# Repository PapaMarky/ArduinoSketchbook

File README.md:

ArduinoLibs
===========

Libraries for Arduino programming

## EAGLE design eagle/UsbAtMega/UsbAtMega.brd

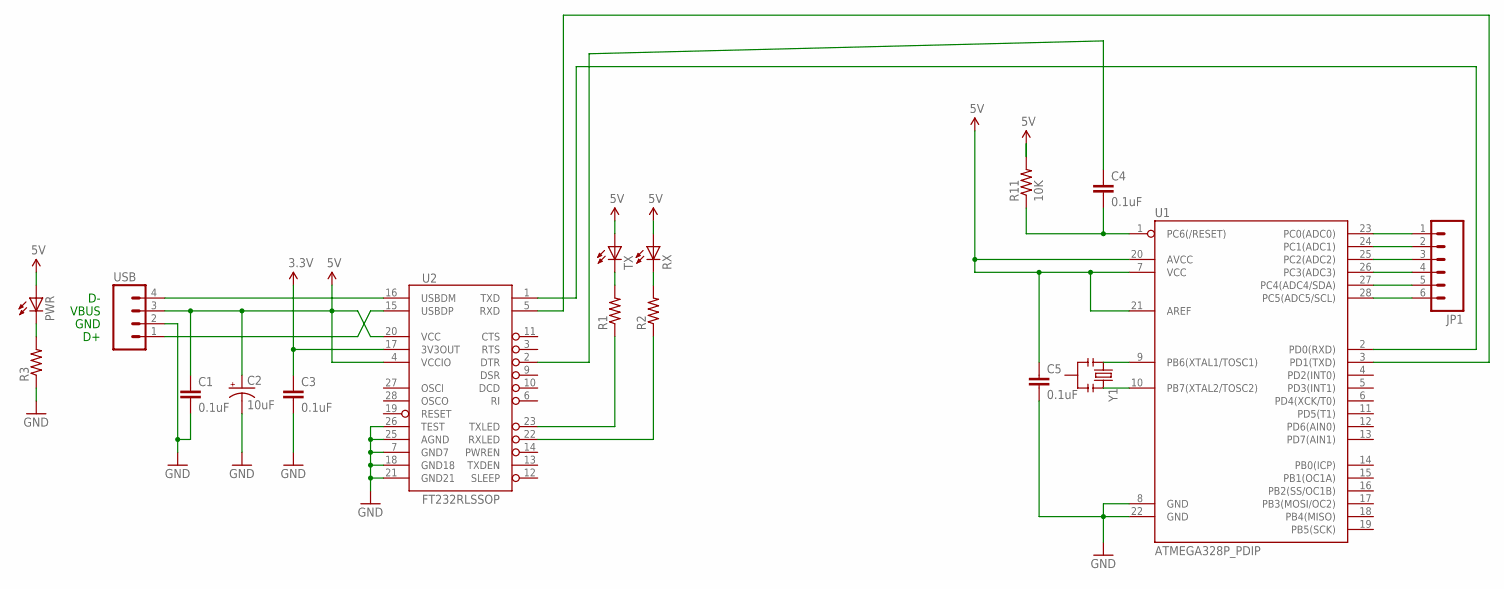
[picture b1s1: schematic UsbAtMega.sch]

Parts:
C1, C3: 0.1uF; CAP-PTH-SMALLEZ
C2: 10uF; CPOL-RADIAL-10UF-25V
C4, C5: 0.1uF; CAP-PTH-SMALL
JP1: M06SIP; 1X06
PWR: LED5MM
R1, R2, R3: 10KOHM1/6W5%(PTH)KIT; AXIAL-0.3-KIT
R11: 10K; AXIAL-0.3
RX: LED5MM
TX: LED5MM
U1: ATMEGA328P_PDIP; DIL28-3
U2: FT232RLSSOP; SSOP28DB
USB: M04LOCK; 1X04_LOCK
Y1: RESONATORPTH; RESONATOR-PTH

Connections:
3.3V: C3.1, U2.17 (3V3OUT)
5V: C1.1, C2.1 (+), C5.1, PWR.A, R11.P$2 (2), RX.A, TX.A, U1.7 (VCC), U1.20 (AVCC), U1.21 (AREF), U2.4 (VCCIO), U2.20 (VCC), USB.3
GND: C1.2, C2.2 (-), C3.2, C5.2, R3.P$1 (1), U1.8 (GND), U1.22 (GND), U2.7 (GND7), U2.18 (GND18), U2.21 (GND21), U2.25 (AGND), U2.26 (TEST), USB.2
unnamed: C4.2, R11.P$1 (1), U1.1 (PC6(/RESET))
unnamed: U2.16 (USBDM), USB.4
unnamed: U2.15 (USBDP), USB.1
unnamed: C4.1, U2.2 (DTR)
unnamed: U1.2 (PD0(RXD)), U2.1 (TXD)
unnamed: U1.3 (PD1(TXD)), U2.5 (RXD)
unnamed: U1.9 (PB6(XTAL1/TOSC1)), Y1.1
unnamed: U1.10 (PB7(XTAL2/TOSC2)), Y1.3
unnamed: JP1.6, U1.28 (PC5(ADC5/SCL))
unnamed: JP1.5, U1.27 (PC4(ADC4/SDA))
unnamed: JP1.4, U1.26 (PC3(ADC3))
unnamed: JP1.3, U1.25 (PC2(ADC2))
unnamed: R1.P$1 (1), U2.23 (TXLED)
unnamed: R2.P$1 (1), U2.22 (RXLED)
unnamed: R1.P$2 (2), TX.K (C)
unnamed: R2.P$2 (2), RX.K (C)
unnamed: PWR.K (C), R3.P$2 (2)
unnamed: JP1.2, U1.24 (PC1(ADC1))
unnamed: JP1.1, U1.23 (PC0(ADC0))

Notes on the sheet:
VBUS
GND

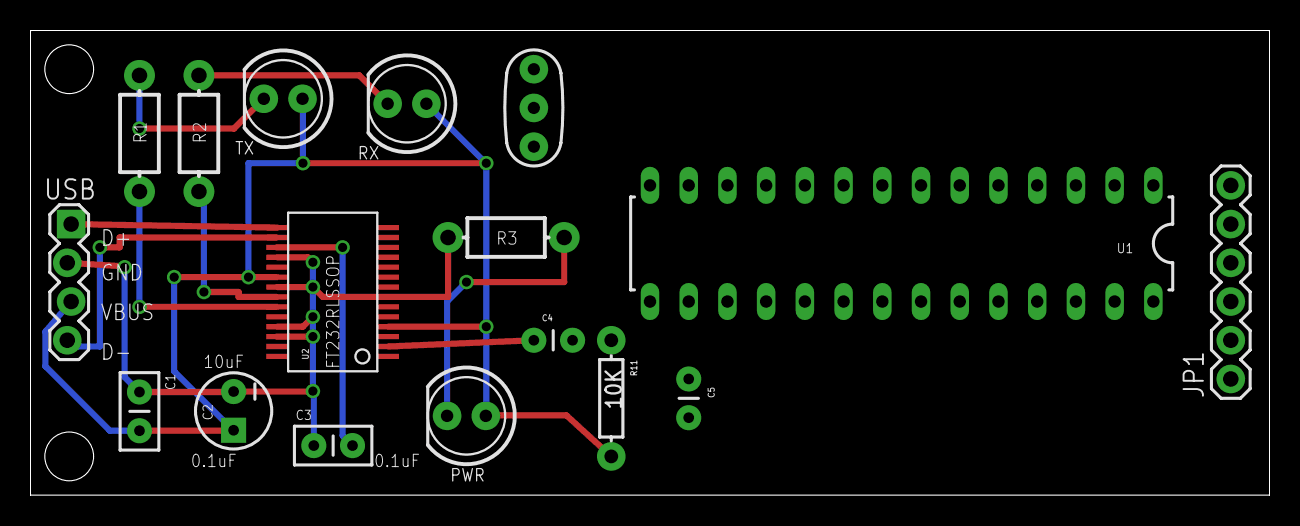
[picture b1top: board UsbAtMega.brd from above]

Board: 2 copper layers, 81.3 x 30.5 mm, 17 parts (0 on the bottom side), 22 nets.

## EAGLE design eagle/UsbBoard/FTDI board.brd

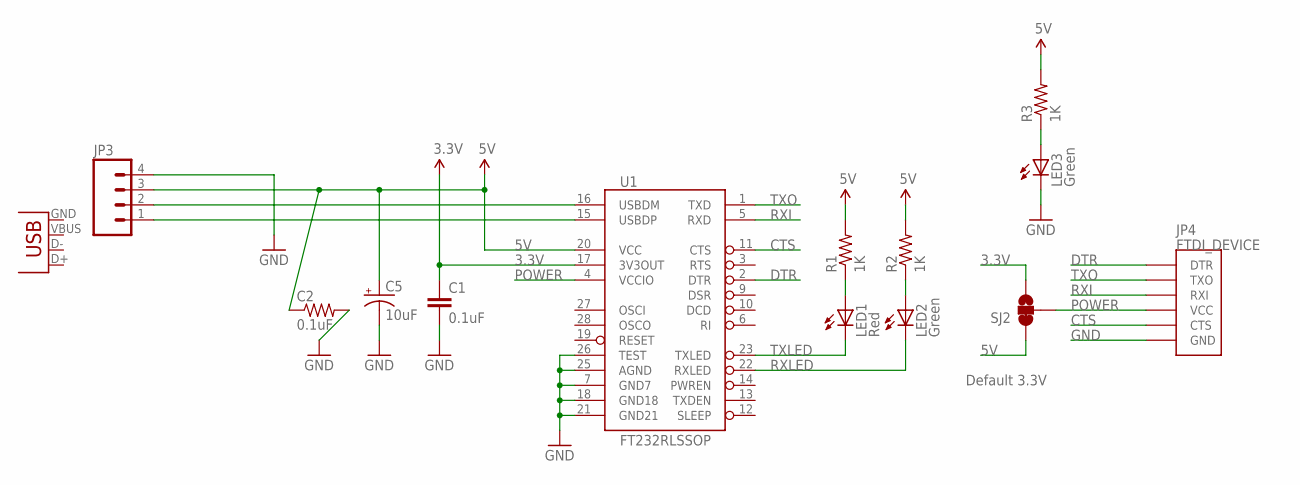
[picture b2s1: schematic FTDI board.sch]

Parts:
C1: 0.1uF; 0402-CAP
C2: 0.1uF; AXIAL-0.1
C5: 10uF; EIA3216
JP3: M04LOCK; 1X04_LOCK
JP4: FTDI_DEVICE; FTDI_DEVICE_SIDE
LED1: Red; LED5MM
LED2, LED3: Green; LED5MM
R1, R2, R3: 1K; AXIAL-0.1
SJ2: SOLDERJUMPER_2WAYS; SJ_3
U1: FT232RLSSOP; SSOP28DB
X1: USB-SMD-NS; USB-MINIB-NOSTOP

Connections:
3.3V: C1.1, SJ2.3, U1.17 (3V3OUT)
5V: C2.P$1 (1), C5.A (+), JP3.3, R1.P$2 (2), R2.P$2 (2), R3.P$2 (2), SJ2.1, U1.20 (VCC)
CTS: JP4.P$5 (CTS), U1.11 (CTS)
DTR: JP4.P$1 (DTR), U1.2 (DTR)
GND: C1.2, C2.P$2 (2), C5.C (-), JP3.4, JP4.P$6 (GND), LED3.K (C), U1.7 (GND7), U1.18 (GND18), U1.21 (GND21), U1.25 (AGND), U1.26 (TEST)
unnamed: LED1.A, R1.P$1 (1)
unnamed: LED2.A, R2.P$1 (1)
unnamed: LED3.A, R3.P$1 (1)
POWER: JP4.P$4 (VCC), SJ2.2, U1.4 (VCCIO)
RXI: JP4.P$3 (RXI), U1.5 (RXD)
RXLED: LED2.K (C), U1.22 (RXLED)
TXLED: LED1.K (C), U1.23 (TXLED)
TXO: JP4.P$2 (TXO), U1.1 (TXD)
USB_D+: JP3.1, U1.15 (USBDP)
USB_D-: JP3.2, U1.16 (USBDM)

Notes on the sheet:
Default 3.3V

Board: 2 copper layers, 14 parts (1 on the bottom side), 15 nets, no tracks yet.

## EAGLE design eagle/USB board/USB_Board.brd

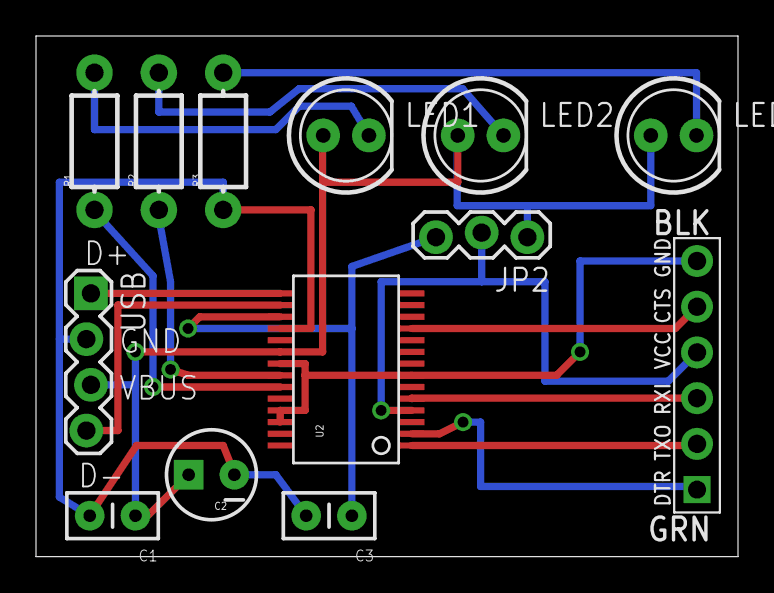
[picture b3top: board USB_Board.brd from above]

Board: 2 copper layers, 39.0 x 28.9 mm, 13 parts (0 on the bottom side), 15 nets.

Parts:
C1, C3: 0.1uF; CAP-PTH-SMALLEZ
C2: 10uF; CPOL-RADIAL-10UF-25V
JP1: FTDI_DEVICE; FTDI_DEVICE_SIDE
JP2: 1X03_LOCK
LED1, LED2, LED3: LED5MM
R1, R2, R3: AXIAL-0.3-KIT
U2: FT232RLSSOP; SSOP28DB
USB: 1X04_LOCK

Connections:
3.3V: C3.1, JP2.3, U2.17
5V: C1.1, C2.1, JP2.1, LED1.A, LED2.A, LED3.A, U2.20, USB.3
GND: C1.2, C2.2, C3.2, JP1.P$6, R3.P$1, U2.7, U2.18, U2.21, U2.25, U2.26, USB.2
unnamed: U2.16, USB.4
unnamed: U2.15, USB.1
unnamed: JP1.P$2, U2.1
unnamed: JP1.P$3, U2.5
unnamed: JP1.P$5, U2.11
unnamed: JP1.P$1, U2.2
unnamed: JP1.P$4, JP2.2, U2.4
unnamed: R1.P$1, U2.23
unnamed: R2.P$1, U2.22
unnamed: LED1.K, R1.P$2
unnamed: LED2.K, R2.P$2
unnamed: LED3.K, R3.P$2

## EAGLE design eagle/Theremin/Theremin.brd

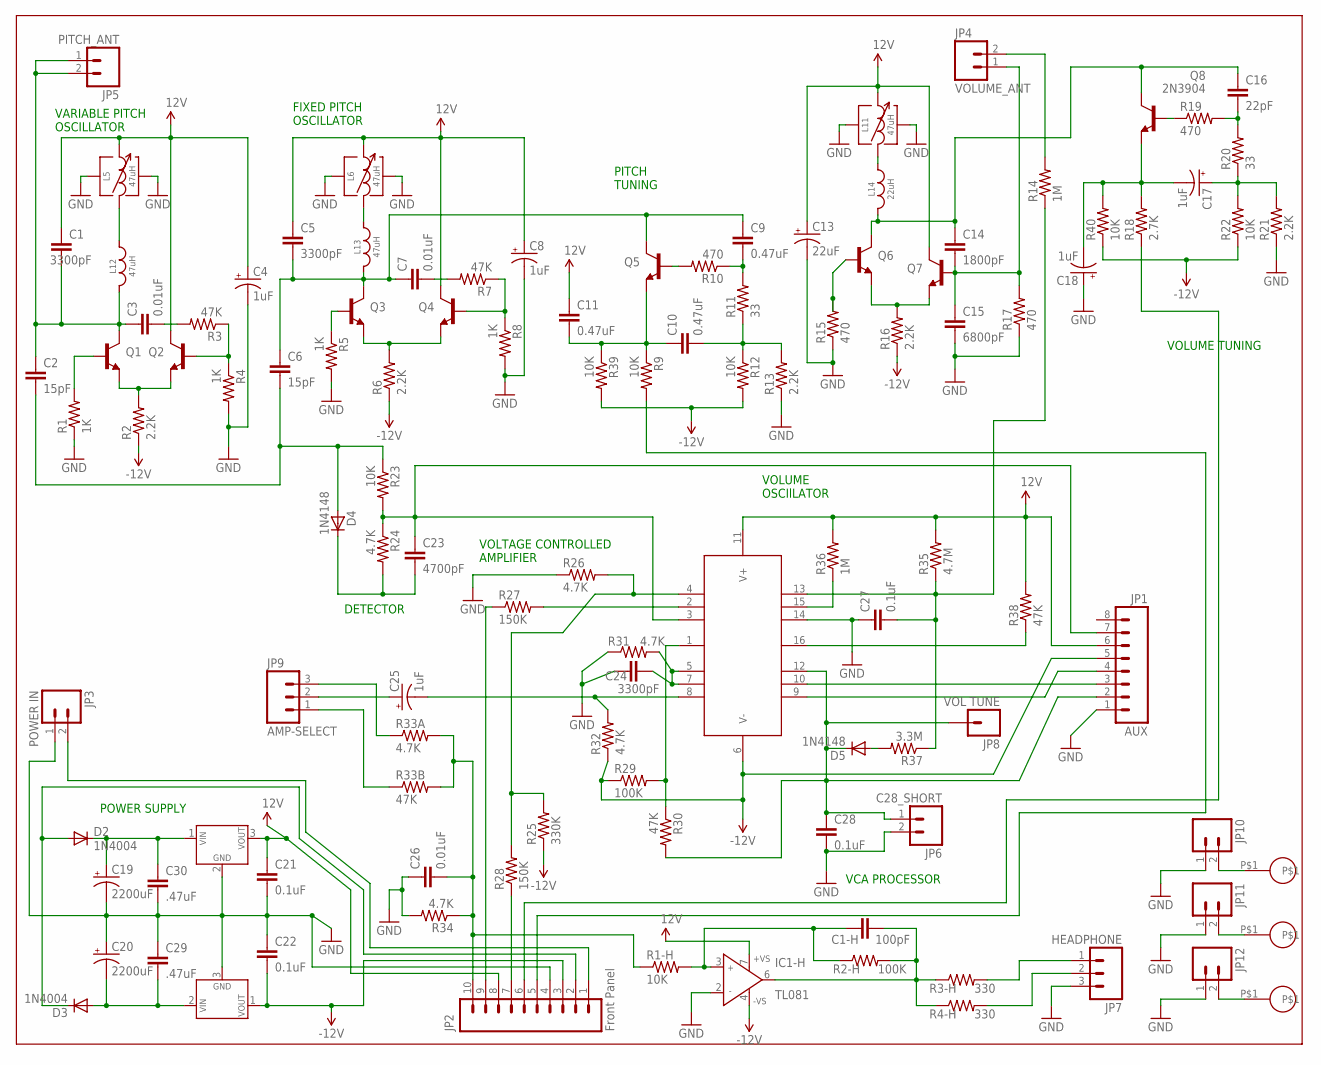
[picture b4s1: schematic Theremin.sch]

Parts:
C1, C5: 3300pF; 9M-CAP-RADIAL
C1-H: 100pF; CAP-PTH-SMALL
C2, C6: 15pF; CAP-PTH-SMALL
C3, C7, C26: 0.01uF; 5M-CAP-RADIAL
C4, C8, C17, C18, C25: 1uF; CPOL-RADIAL-10UF-25V
C9, C10, C11: 0.47uF; CAP-PTH-5MM
C13: 22uF; CPOL-RADIAL-1000UF-25V
C14: 1800pF; CAP-PTH-LARGE
C15: 6800pF; C5B3
C16: 22pF; CAP-PTH-SMALLEZ
C19, C20: 2200uF; 10MM-RADIAL-CPOL
C21, C22, C27, C28: 0.1uF; CAP-PTH-SMALL
C23: 4700pF; CAP-PTH-SMALL
C24: 3300pF; CAP-PTH-SMALL
C29, C30: .47uF; AXIAL-5MM
D2, D3: 1N4004; DO41-10
D4, D5: 1N4148; DIODE-1N4148
IC1-H: TL081; DIL08
JP1: AUX; 1X08
JP2: Front Panel; 1X10
JP3: POWER IN; 1X02_NO_SILK
JP4: VOLUME_ANT; 1X02_NO_SILK
JP5: PITCH_ANT; 1X02_NO_SILK
JP6: C28_SHORT; 1X02_LOCK
JP7: HEADPHONE; 1X03_NO_SILK
JP8: VOL TUNE; 1X01_LONGPAD
JP9: AMP-SELECT; 1X03_LOCK
JP10, JP11, JP12: M02LOCK; 1X02_LOCK
L5, L6, L11: 47uH; SLOT-TEN
L12, L13: 47uH; FIXED-INDUCTOR-API-DELEVAN
L14: 22uH; FIXED-INDUCTOR-API-DELEVAN
Q1, Q2, Q3, Q4, Q5, Q6, Q7, Q8: 2N3904; TO92
R1, R4, R5, R8: 1K; AXIAL-0.4
R1-H, R9, R12, R22, R23, R39, R40: 10K; AXIAL-0.4
R2, R6, R13, R16, R21: 2.2K; AXIAL-0.4
R2-H, R29: 100K; AXIAL-0.4
R3, R7, R30, R33B, R38: 47K; AXIAL-0.4
R3-H, R4-H: 330; AXIAL-0.4
R10, R15, R17, R19: 470; AXIAL-0.4
R11, R20: 33; AXIAL-0.4
R14, R36: 1M; AXIAL-0.4
R18: 2.7K; AXIAL-0.4
R24, R26, R31, R32, R33A, R34: 4.7K; AXIAL-0.4
R25: 330K; AXIAL-0.4
R27, R28: 150K; AXIAL-0.4
R35: 4.7M; AXIAL-0.4
R37: 3.3M; AXIAL-0.4
U1: LM78L12; TO-92
U2: LM79L12; TO-92
U3: LM13700N; DIL16
U$1, U$2, U$3: GROUND-SCREW

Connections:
5V: C1.P$1 (1), C4.1 (+), C5.P$1 (1), C8.1 (+), C11.1, C13.1 (+), C21.1, IC1-H.7 (+VS), JP1.6, JP2.8, L5.IN$1, L6.IN$1, L11.IN$1, Q2.1 (C), Q4.1 (C), Q7.1 (C), R35.P$2 (2), R36.P$2 (2), R38.P$2 (2), U1.3 (VOUT), U3.11 (V+)
-12V: JP1.5, R2.P$1 (1), R16.P$1 (1), R22.P$1 (1), R29.P$1 (1), R32.P$1 (1), R40.P$1 (1), U3.6 (V-)
GND: C4.2 (-), C8.2 (-), C13.2 (-), C15.2, C18.1 (+), C19.P$2 (-), C20.P$1 (+), C21.2, C22.1, C24.1, C26.P$1 (1), C27.1, C28.2, C29.P$1 (1), C30.P$2 (2), IC1-H.2 (IN-), JP1.1, JP2.4, JP3.1, JP6.2, JP7.3, JP10.1, JP11.1, JP12.1, L5.TAB@7, L5.TAB@8, L6.TAB@7, L6.TAB@8, L11.TAB@7, L11.TAB@8, R1.P$1 (1), R4.P$2 (2), R5.P$2 (2), R8.P$2 (2), R13.P$1 (1), R15.P$1 (1), R17.P$1 (1), R21.P$1 (1), R26.P$1 (1), R31.P$1 (1), R34.P$2 (2), U1.2 (GND), U2.3 (GND), U3.14 (IN-PLUS-B)
unnamed: Q8.2 (B), R19.P$1 (1)
unnamed: C16.2, R19.P$2 (2), R20.P$2 (2)
unnamed: C17.1 (+), R20.P$1 (1), R21.P$2 (2), R22.P$2 (2)
unnamed: C14.1, C16.1, L14.P$2, Q6.1 (C), Q8.1 (C)
unnamed: C17.2 (-), C18.2 (-), Q8.3 (E), R18.P$2 (2), R40.P$2 (2)
unnamed: Q6.3 (E), Q7.3 (E), R16.P$2 (2)
unnamed: JP2.6, R18.P$1 (1)
unnamed: Q6.2 (B), R15.P$2 (2)
unnamed: C14.2, C15.1, JP4.1, Q7.2 (B), R17.P$2 (2)
unnamed: L5.OUT$3 (OUT$2), L12.P$1
unnamed: L11.OUT$3 (OUT$2), L14.P$1
unnamed: C20.P$2 (-), C29.P$2 (2), D3.A, U2.2 (VIN)
unnamed: C19.P$1 (+), C30.P$1 (1), D2.C, U1.1 (VIN)
unnamed: D2.A, D3.C, JP2.2
unnamed: JP4.2, R14.P$2 (2)
unnamed: Q1.2 (B), R1.P$2 (2)
unnamed: C1.P$2 (2), C2.1, C3.P$1 (1), JP5.1, JP5.2, L12.P$2, Q1.1 (C)
unnamed: Q1.3 (E), Q2.3 (E), R2.P$2 (2)
unnamed: Q2.2 (B), R3.P$1 (1), R4.P$1 (1)
unnamed: C2.2, C6.2, D4.A, R23.P$1 (1)
unnamed: R38.P$1 (1), U3.16 (BIAS-IN-B)
unnamed: JP1.3, U3.10 (B-IN-B)
unnamed: JP1.4, U3.9 (B-OUT-B)
unnamed: C28.1, D5.C, JP1.2, JP6.1, JP8.1, R30.P$2 (2), U3.12 (OUT-B)
unnamed: D5.A, R37.P$2 (2)
unnamed: C27.2, R14.P$1 (1), R35.P$1 (1), R37.P$1 (1), U3.13 (IN-MINUS-B)
unnamed: R29.P$2 (2), R30.P$1 (1), U3.1 (BIAS-IN-A)
unnamed: R36.P$1 (1), U3.15 (DIODE-BIAS-B)
unnamed: C25.2 (-), R32.P$2 (2), U3.8 (B-OUT-A)
unnamed: C25.1 (+), JP9.2
unnamed: C1-H.1, IC1-H.3 (IN+), R1-H.P$2 (2), R2-H.P$1 (1)
unnamed: C24.2, R31.P$2 (2), U3.5 (OUT-A), U3.7 (B-IN-A)
unnamed: R27.P$2 (2), U3.2 (DIODE-BIAS-A)
unnamed: JP2.9, R27.P$1 (1)
unnamed: JP2.7, R28.P$1 (1)
unnamed: R25.P$2 (2), R26.P$2 (2), R28.P$2 (2), U3.4 (IN-MINUS-A)
unnamed: C23.1, JP1.7, R23.P$2 (2), R24.P$1 (1), U3.3 (IN-PLUS-A)
unnamed: C23.2, D4.C, R24.P$2 (2)
unnamed: JP2.1, JP3.2
unnamed: C3.P$2 (2), R3.P$2 (2)
unnamed: C5.P$2 (2), C6.1, C7.P$1 (1), C9.1, L13.P$2, Q3.1 (C), Q5.1 (C)
unnamed: Q3.2 (B), R5.P$1 (1)
unnamed: Q3.3 (E), Q4.3 (E), R6.P$2 (2)
unnamed: L6.OUT$3 (OUT$2), L13.P$1
unnamed: C10.1, C11.2, Q5.3 (E), R9.P$1 (1), R39.P$1 (1)
unnamed: C7.P$2 (2), R7.P$2 (2)
unnamed: JP2.5, R9.P$2 (2)
unnamed: Q4.2 (B), R7.P$1 (1), R8.P$1 (1)
unnamed: Q5.2 (B), R10.P$2 (2)
unnamed: C9.2, R10.P$1 (1), R11.P$2 (2)
unnamed: C10.2, R11.P$1 (1), R12.P$1 (1), R13.P$2 (2)
unnamed: JP9.3, R33A.P$1 (1)
unnamed: JP9.1, R33B.P$1 (1)
unnamed: C26.P$2 (2), JP2.10, R1-H.P$1 (1), R33A.P$2 (2), R33B.P$2 (2), R34.P$1 (1)
unnamed: C1-H.2, IC1-H.6 (OUT), R2-H.P$2 (2), R3-H.P$1 (1), R4-H.P$1 (1)
unnamed: JP7.1, R3-H.P$2 (2)
unnamed: JP7.2, R4-H.P$2 (2)
unnamed: JP10.2, U$2.P$1
unnamed: JP11.2, U$1.P$1
unnamed: JP12.2, U$3.P$1
VNEG: C22.2, IC1-H.4 (-VS), JP2.3, R6.P$1 (1), R12.P$2 (2), R25.P$1 (1), R39.P$2 (2), U2.1 (VOUT)

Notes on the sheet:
VOLUME TUNING
VOLUME OSCIlLATOR
POWER SUPPLY
VARIABLE PITCH OSCILLATOR
VCA PROCESSOR
VOLTAGE CONTROLLED AMPLIFIER
DETECTOR
FIXED PITCH OSCILLATOR
PITCH TUNING

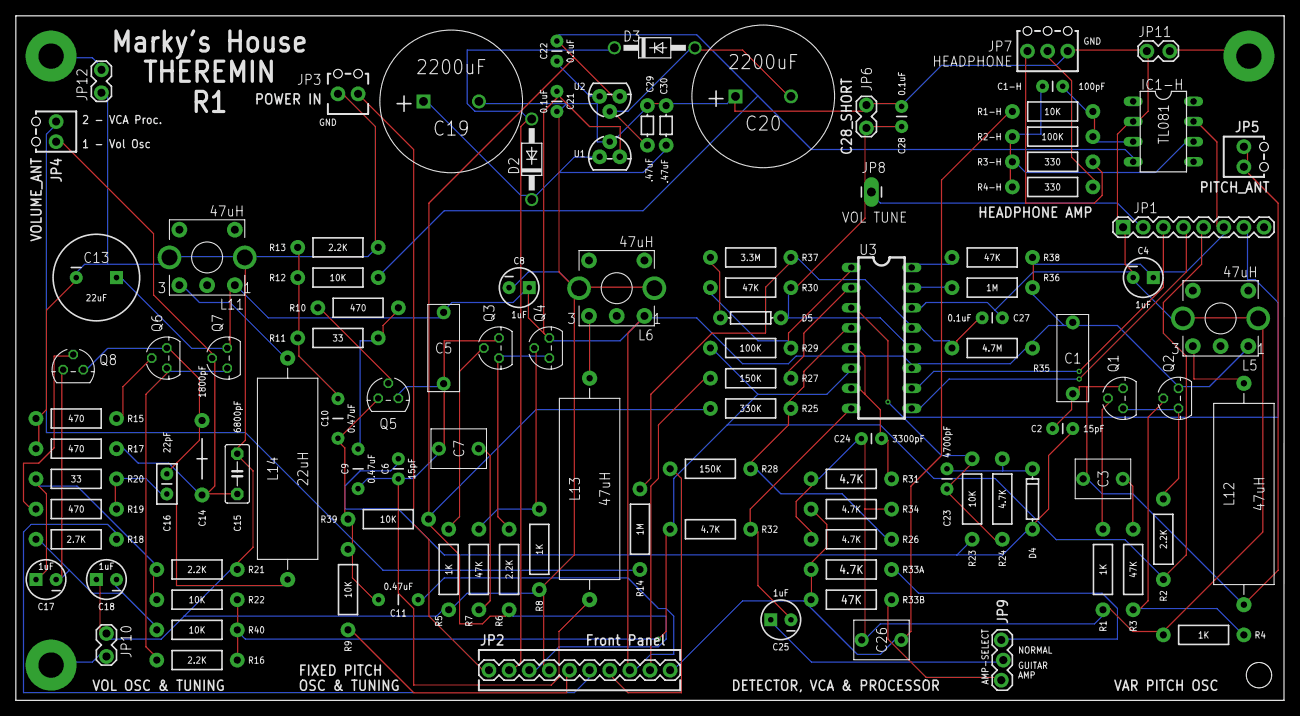
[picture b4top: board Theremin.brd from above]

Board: 2 copper layers, 160.0 x 86.4 mm, 112 parts (0 on the bottom side), 64 nets.

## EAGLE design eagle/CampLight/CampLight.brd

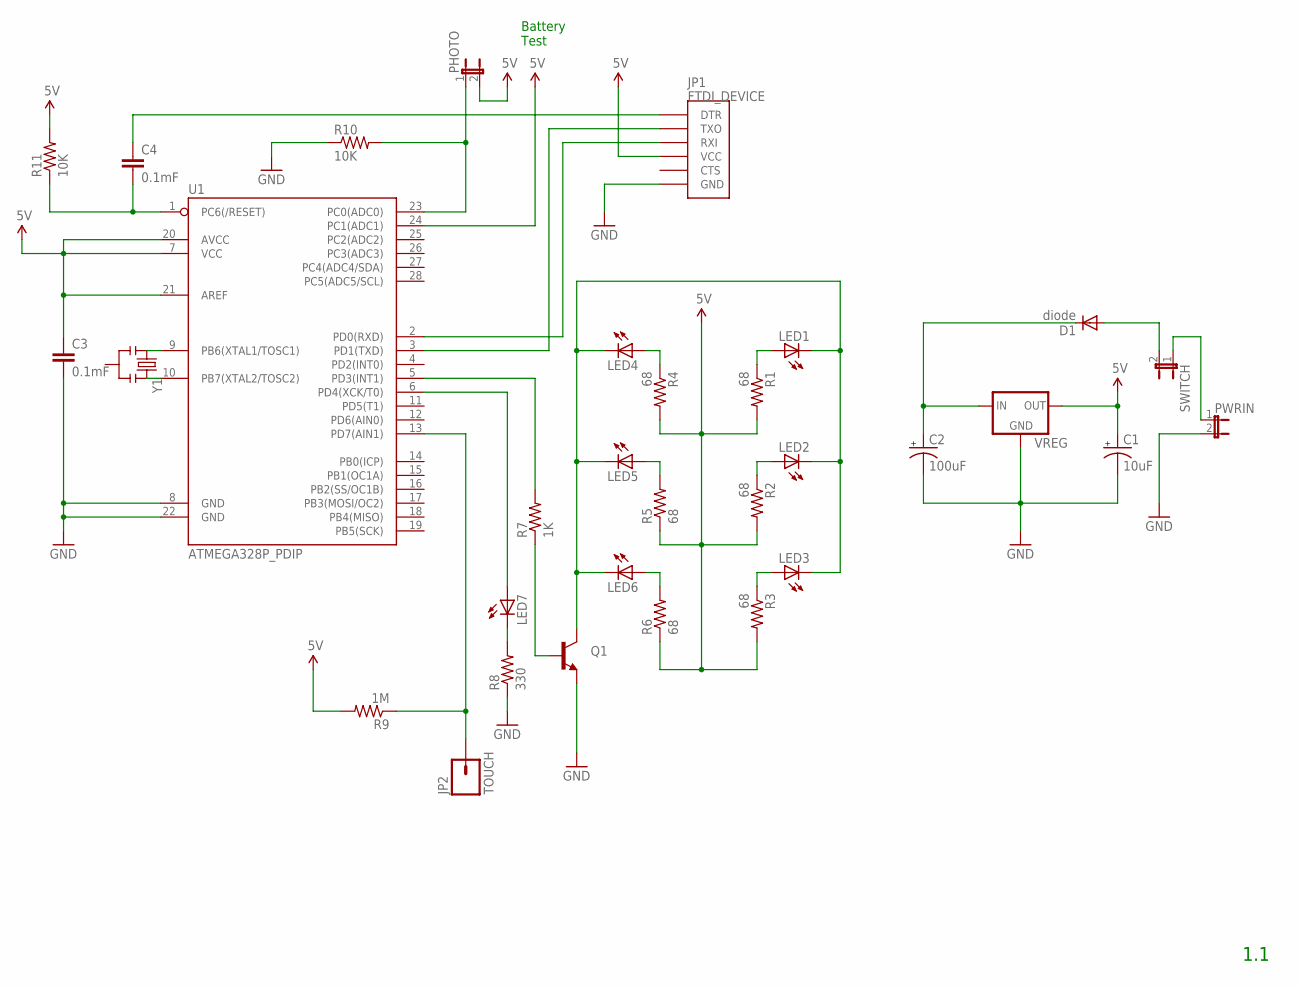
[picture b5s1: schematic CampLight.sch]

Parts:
C1: 10uF; CPOL-RADIAL-10UF-25V
C2: 100uF; CPOL-RADIAL-10UF-25V
C3, C4: 0.1mF; CAP-PTH-SMALL
D1: diode; DIODE-1N4001
JP1: FTDI_DEVICE; FTDI_DEVICE_SIDE
JP2: TOUCH; 1X01
LED1, LED2, LED3, LED4, LED5, LED6: LED5MM
LED7: LED3MM
PHOTO: JUMPER-2PTH_LOCK; 1X02_LOCK
PWRIN: JUMPER-2PTH_LOCK; 1X02_LOCK
Q1: TRANSISTOR_NPNTO-92-AMMO; TO-92-AMMO
R1, R2, R3, R4, R5, R6: 68; AXIAL-0.3
R7: 1K; AXIAL-0.4
R8: 330; AXIAL-0.3
R9: 1M; AXIAL-0.4
R10, R11: 10K; AXIAL-0.3
SWITCH: JUMPER-2PTH_LOCK; 1X02_LOCK
U1: ATMEGA328P_PDIP; DIL28-3
VREG: 78LXX
Y1: RESONATORPTH; RESONATOR-PTH

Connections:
5V: C1.1 (+), C3.1, JP1.P$4 (VCC), PHOTO.2, R1.P$2 (2), R2.P$2 (2), R3.P$2 (2), R4.P$2 (2), R5.P$1 (1), R6.P$1 (1), R9.P$2 (2), R11.P$2 (2), U1.7 (VCC), U1.20 (AVCC), U1.21 (AREF), U1.24 (PC1(ADC1)), VREG.OUT
GND: C1.2 (-), C2.2 (-), C3.2, JP1.P$6 (GND), PWRIN.2, Q1.1 (E), R8.P$1 (1), R10.P$1 (1), U1.8 (GND), U1.22 (GND), VREG.GND
unnamed: C2.1 (+), D1.C, VREG.IN
unnamed: PWRIN.1, SWITCH.1
unnamed: U1.9 (PB6(XTAL1/TOSC1)), Y1.1
unnamed: U1.10 (PB7(XTAL2/TOSC2)), Y1.3
unnamed: D1.A, SWITCH.2
unnamed: R7.P$2 (2), U1.5 (PD3(INT1))
unnamed: LED1.K (C), LED2.K (C), LED3.K (C), LED4.K (C), LED5.K (C), LED6.K (C), Q1.3 (C)
unnamed: LED4.A, R4.P$1 (1)
unnamed: LED5.A, R5.P$2 (2)
unnamed: LED1.A, R1.P$1 (1)
unnamed: LED6.A, R6.P$2 (2)
unnamed: JP1.P$3 (RXI), U1.2 (PD0(RXD))
unnamed: LED2.A, R2.P$1 (1)
unnamed: LED3.A, R3.P$1 (1)
unnamed: JP1.P$2 (TXO), U1.3 (PD1(TXD))
unnamed: C4.2, R11.P$1 (1), U1.1 (PC6(/RESET))
unnamed: C4.1, JP1.P$1 (DTR)
unnamed: Q1.2 (B), R7.P$1 (1)
unnamed: LED7.K (C), R8.P$2 (2)
unnamed: LED7.A, U1.6 (PD4(XCK/T0))
unnamed: JP2.1, R9.P$1 (1), U1.13 (PD7(AIN1))
unnamed: PHOTO.1, R10.P$2 (2), U1.23 (PC0(ADC0))

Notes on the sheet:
Battery Test
1.1

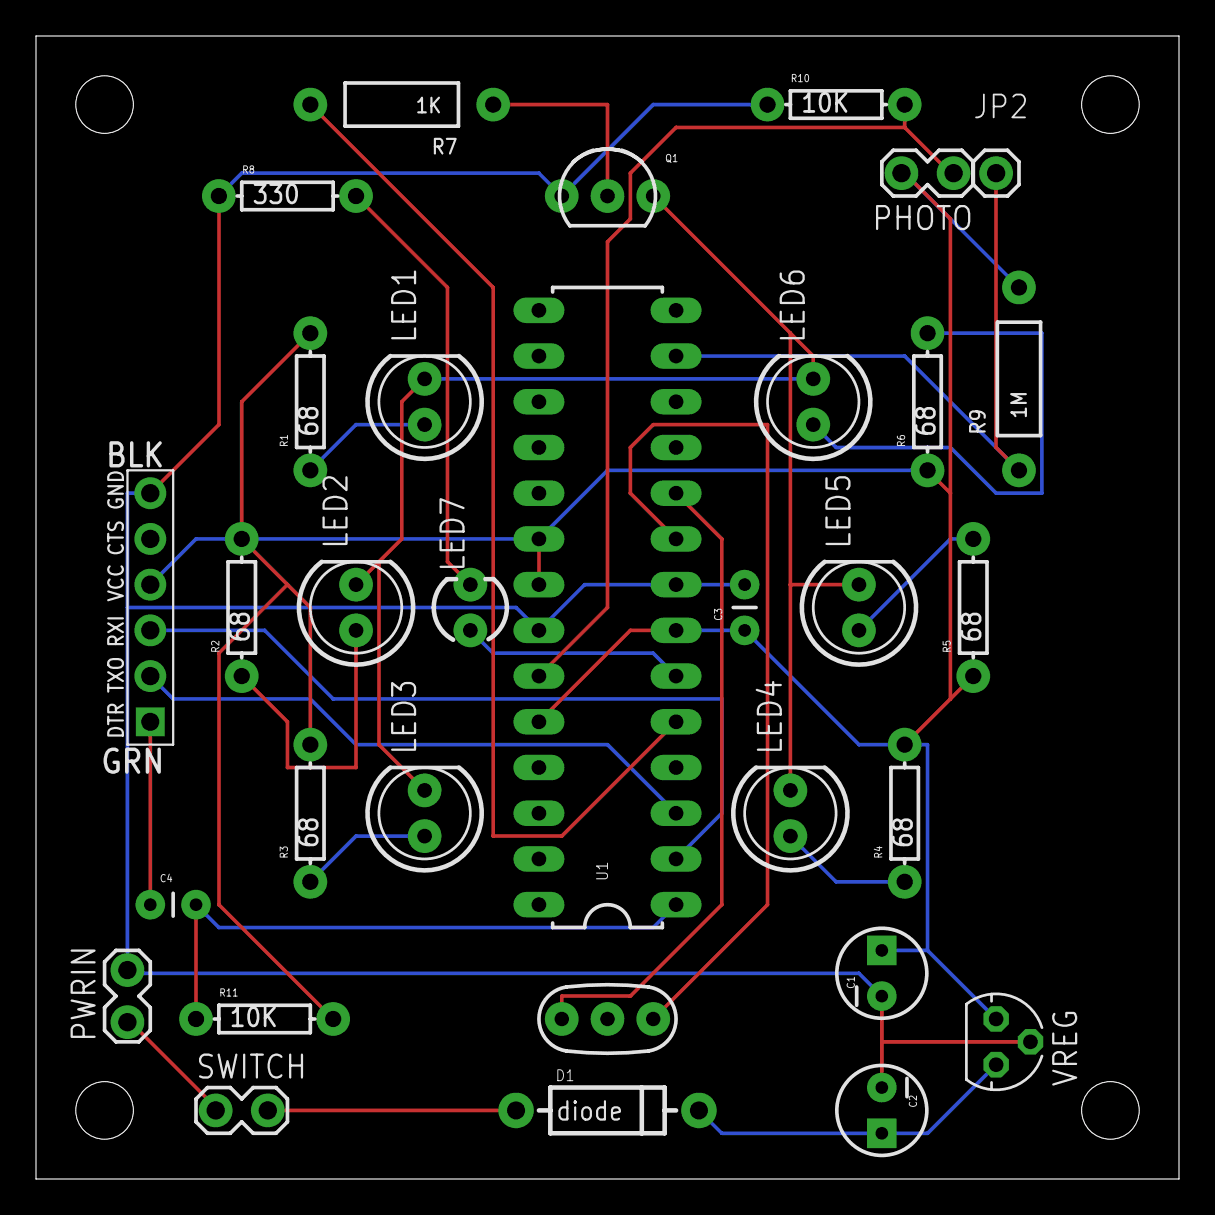
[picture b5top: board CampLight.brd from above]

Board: 2 copper layers, 63.5 x 63.5 mm, 32 parts (0 on the bottom side), 24 nets.

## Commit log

2013-02-02 initial commit of existing stuff
2013-02-02 add .gitignore
2013-02-03 Add notes.txt to Booze O Meter
2013-02-12 SAC: checkpoint work
2013-02-12 BOM: improve class structure
2013-02-13 Add RGB_LED & get sensors working
2013-02-17 Add fritzing of prototype
2013-04-20 refactor: split StateContext out of Booze_O_Meter, and parts out of StateContext
2013-04-29 refactor Booze_O_Meter class out of existance.
    * move main button into sketchbook
    * move setup functionality into sketchbook
2013-04-29 document state machine
2013-06-10 add lighted button and lots of refactoring
2013-07-20 Make the 7 segment display do cool stuff at start up
2013-07-20 add libraries as submodule
2013-08-21 Add CampLamp project
2013-08-29 Latest Camplight work
2013-08-29 I don't want 'libraries' to be a submodule
2013-08-29 Add 'libraries' as a subdirectory instead of a submodule
2013-08-29 Convert SwissArmyClock to a subdirectory instead of a sub module
2013-08-29 update camplight eagle file
2013-08-29 deleted 'libraries'
2013-08-29 add libraries as directory not a submodule
2013-08-29 put SwissArmyClock back, as a subdirectory
2013-08-30 Move files
2013-09-10 start work on touch switch
2013-09-10 add doxygen docs
2013-09-14 missed adding these files
2013-09-14 Continue work on Camp Lamp * Add readCapacitivePin( ) - now I have a reliable touch switch * Add state machine diagram * Add NOTES.txt file with links to resources
2013-09-15 Have stable touch switch HW& SW
2013-09-15 Update eagle files with touch switch
    This is a final release candidate. I have sent this board to Osh Park (oshpark.com) for fabrication.
2013-10-05 Update camplight eagle files * Add pull up resistor to reset pin * reverse R & T on programming header
2013-10-05 start the theremin project
2013-10-06 Basic state machine infrastructure
2013-10-06 Implement TouchSwitch based on readCapacitivePin
2013-10-06 Implement BatteryMonitor
2013-10-06 setup boilerplate for states
2013-10-06 implement OnState and OffState
2013-10-06 Implement AdjustBrightnessState
2013-10-06 Bug fixes
    * Battery_level was looking at the wrong pin
    * OnState & OffState were looking at the wrong thresholds
    * AdjustBrightnessState wasn't smooth when switch held & released multiple times
2013-10-06 Tweak Touch sensor label
2013-10-08 threshhold for touch sensor was too high. Now it all works off of battery! :-)
2013-10-13 Theremin board design
2013-12-04 get everything committed to move to new machine
2013-12-04 not sure if I need any of this committing the lot rather than risk loosing something
2013-12-07 Add big capacitors to theremin power supply
2013-12-28 Added Variable Pitch Oscillator cleaned up layout of schematic
2013-12-29 Added LM13600, VCA Processor, headers
2013-12-31 Work on VOLTAGE CONTROLLED AMPLIFIER section
2013-12-31 Finish VOLTAGE CONTROLLED AMP, add DETECTOR
2013-12-31 work on POWER SUPPLY
2014-01-05 Add the FIXED PITCH OSCILLATOR curcuit
2014-01-05 Add PITCH TUNING curcuit
2014-01-18 Add jumper and resistor for selecting output amp type
    Normal (keyboard, stereo) and Guitar / Bass
2014-01-19 Layout for Antennae Boards
2014-01-20 Clean up board layout
2014-01-20 Add headphone amp
    various tweaks
2014-01-22 Various tweaks and improvements.
    The board is routed.
2014-01-25 Finalized board layout
2014-02-03 Update RTC library
    from Adafruit for use with data logger shield
2014-03-12 Add libraries used for DataLogger
2014-03-12 Theremin changes.
2014-03-12 Add Apu work
2014-03-12 Audio fun
2014-03-12 Theremin Jumper notes
2014-03-12 avr programmer
2014-03-14 Checkpoint DAC music generator work.
    Current version doesn't work. I'm guessing that it is too slow. Will try to make things faster.
2014-06-28 DAC player
2014-06-28 Baseline FTDI board design from SparkFun
2014-06-28 Replace Usb with header
2014-07-04 First shot at USB board
2014-07-04 checkpoint b4 move led
2014-07-07 First version of USB Board
    Oops, forgot to put in drill holes.
2014-07-26 V1.0 of USB Thang
2014-08-20 Create UsbAtMega from USB_Board
2014-08-20 Add AtMega and hook up pwr & usb
2014-08-28 Initial work on NeoDigits
2014-08-28 Begin LED_Circle_Clock project
    * Add processing program to generate clock frame template
2014-08-28 Separate setup for PNG and single Letter size page
2014-08-28 Improve 'letter' version of template generator.
    Now it draws several copies offset across the page.
2014-08-29 tweaks
2014-08-30 Use values measured from actual foamboard prototype
2014-09-04 more tweaks to circle clock template generator
2014-09-05 Start Manual routing
2014-09-05 Finish manual routing for USB <--> AtMega
2014-09-06 Experiments repositioning AtMega to try to get something shield-able.
2014-09-11 Create Shape FinishLine project
2014-09-12 start fleshing out architecture
2014-09-12 Start work on state machine
2014-09-30 simple 'bring up' experiments
2014-10-01 Start work on the DataBase class implementation.
2014-10-01 Add LCD to FinishLine
2014-10-01 FinishLine: work on LCD class
2014-10-02 FinishLine: Work on state machine
2014-10-03 FinishLine: Get start up sorted a little bit
2014-10-03 FinishLine: add Timer class
    Still need to hook up firing of event.
2014-10-04 FinishLine: Work on timer & powerup
2014-10-09 UsbAtMega: upgrade to eagle 7
2014-10-20 NeoDigit work. Digits for big digital clock.
    Will probably move to sketch someday.
2014-10-21 BigDigitalClock: checkpoint - got it to compile
2014-11-01 BigDigitalClock: Single digit tested and working
2015-01-13 update (?) LiquidCrystal library
2015-01-13 Add TinyWire Library
2015-01-13 Get BigDigitalClock up to date
2015-01-13 NeoDigits tweaks
2015-01-13 add Adafruit NeoPixel library
2015-01-13 Add AutoLocker project for locking screen at work
2015-01-13 Work on LED_Circle_Clock
2015-01-13 add ShiftLCD library
2015-01-13 add Super Cool project code
2015-01-13 add phenopitxISP
2015-01-13 add various documentation files
2015-01-13 add simple blink sketch for testing attinys
2015-01-13 add various test sketches
2015-01-13 Start Documenting Shape Stuff
2015-01-13 add PDFs
2015-01-21 Finish Line: Get minimal code to build
    * Take out all HW but LaserAssembly
    * Improve state machine stuff
2015-01-24 FinishLine: Test communication between Base and Lcd processors
2015-02-09 FinishLine: base & LCD communicate, LCD writes to LCD
2015-02-25 FinishLine: Have most of the control panel wired up and tested.
2015-03-19 DataRecorder: minor changes
2015-03-19 FinishLine: Way overdue checkpoint
2015-03-23 SCOOTER BOT: Framework going
    Have communications between lid & base, simplified state machine in base, simplified screens laid out in lid.
2015-03-26 FINISH LINE: Mostly working up through CountdownScreen
2015-03-26 FINISH LINE: Make the lid start over if the base restarts.
2015-03-26 FINISH LINE: fix 'laser seen/laser ready' logic boo boo
2015-04-04 FINISH LINE: Checkpoint: start foul & countdown screen/states
2015-04-04 FINISH LINE: Foul Screen basics working
2015-04-06 FINISH LINE: Countdown screen starts (but doesn't know when to quit)
2015-04-07 FINISH LINE: 1.0 complete

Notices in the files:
parts and their libraries:
SparkFun-DigitalIC: Licensing: CC v3.0 Share-Alike You are welcome to use this library for commercial purposes.
